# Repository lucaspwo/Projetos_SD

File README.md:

# Projetos SD

#### Repositório de códigos para os projetos da disciplina Sistemas Digitais, do curso de Engenharia da Computação - UFRN @ 2018.2

---

[Mini Projeto 1: Simulador de despertador com sensores de luminosidade e temperatura](https://github.com/lucaspwo/Projetos_SD/tree/master/U1_Mini_Projeto_1)

[Mini Projeto 2: MP1 + contador de tempo (30s) via interrupções](https://github.com/lucaspwo/Projetos_SD/tree/master/U1_Mini_Projeto_2)

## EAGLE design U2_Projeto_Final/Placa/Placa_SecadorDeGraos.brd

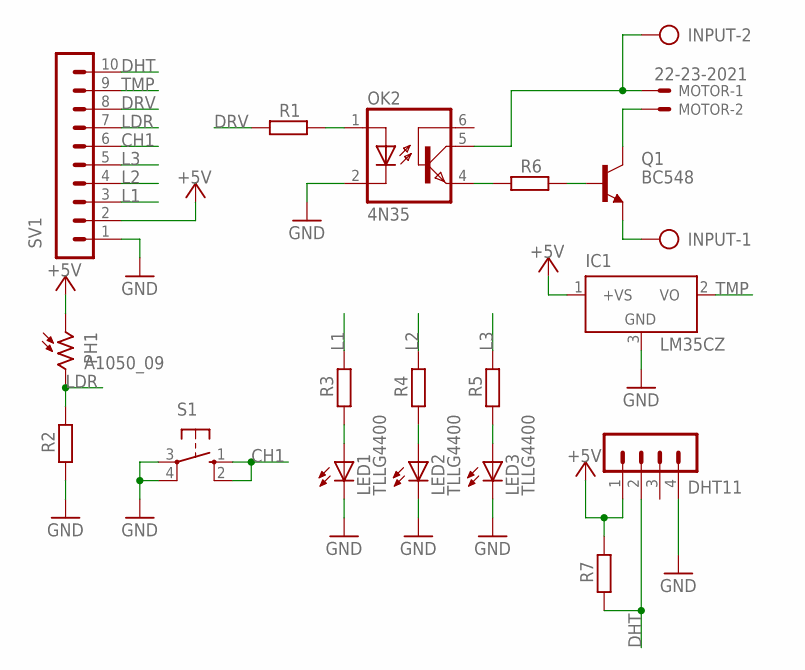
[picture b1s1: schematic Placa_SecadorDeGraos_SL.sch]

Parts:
DHT11: MA04-1
IC1: LM35CZ; TO92
INPUT: AK500/2
LED1, LED2, LED3: TLLG4400; LED3MM
MOTOR: 22-23-2021
OK2: 4N35; DIL06
PH1: A1050_09; T0-46-A10XX
Q1: BC548; TO92-EBC
R1, R2, R3, R4, R5, R6, R7: R-EU_0204/7; 0204/7
S1: 10-XX; B3F-10XX
SV1: MA10-1

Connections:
+5V: DHT11.1, IC1.1 (+VS), PH1.1, R7.2, SV1.2
CH1: S1.1 (S), S1.2 (S1), SV1.6
DHT: DHT11.2, R7.1, SV1.10
DRV: R1.1, SV1.8
GND: DHT11.4, IC1.3 (GND), LED1.K (C), LED2.K (C), LED3.K (C), OK2.2 (C), R2.1, S1.3, S1.4 (P1), SV1.1
L1: R3.2, SV1.3
L2: R4.2, SV1.4
L3: R5.2, SV1.5
LDR: PH1.2, R2.2, SV1.7
unnamed: LED1.A, R3.1
unnamed: LED2.A, R4.1
unnamed: LED3.A, R5.1
unnamed: MOTOR.2, Q1.C
unnamed: OK2.1 (A), R1.2
unnamed: Q1.B, R6.2
unnamed: OK2.4 (EMI), R6.1
unnamed: INPUT.2, MOTOR.1, OK2.5 (COL)
unnamed: INPUT.1, Q1.E
TMP: IC1.2 (VO), SV1.9

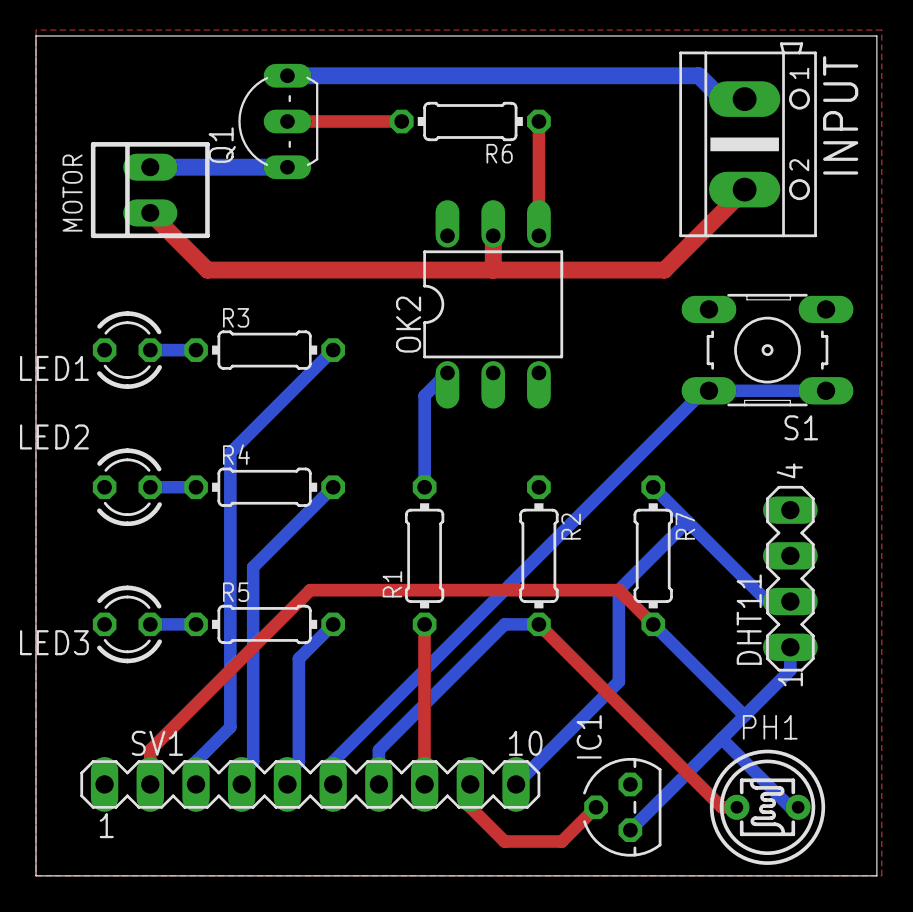
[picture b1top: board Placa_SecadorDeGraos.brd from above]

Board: 2 copper layers, 46.7 x 46.7 mm, 19 parts (0 on the bottom side), 19 nets.

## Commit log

2018-08-18 Upload do primeiro código + arquivos úteis
2018-08-18 Upload do esquemático
2018-08-18 Add comentários no código
2018-08-19 Código finalizado
2018-08-19 Esquemático atualizado
2018-08-19 Correção na conversão de lux para lumen
2018-08-19 Rename Projeto1.md to ReadMe.md
2018-08-19 Mod. no valor de lumens de saída
2018-08-22 Add Mini Projeto 2
2018-08-30 Peq. modificações
2018-09-18 Testes iniciais p/ PU1
2018-09-18 Leitura DHT+LDR - OK
2018-09-18 PU1+botão liga
2018-10-04 Add Placa de secador de grãos
2018-10-04 Add LM35 + DHT11
2018-10-04 mil -> mm
2018-10-04 Peq. atualizações
2018-10-05 Add Protótipo dos códigos
2018-10-05 Add Placa de face simples
2018-10-05 Melhorias no arq do servidor
2018-10-08 Código 80% completo
2018-10-08 Código 85% concluído
2018-10-08 Código 90% concluído + DHT via I2C
2018-10-09 Código 99,9% concluído
    Faltou apenas um comando para terminar a execução das threads
2018-10-16 Projeto 2 100% funcional
2018-10-16 Tratamento de exceções
2018-10-16 Limpeza do código + imagens placa
2018-10-18 Código servidor.py comentado
2018-10-18 Alterações no código DHT_I2C.ino comentadas
2018-10-22 Add Exame_2
2018-10-22 Códigos comentados + imagens e prova
2018-10-24 Peq. modificações + exame 1
